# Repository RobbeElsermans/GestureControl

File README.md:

# Gesture Controlling 

Gesture controlling with X-NUCLEO-53L3A2 DevKit.

Developed by Robbe Elsermans With ED&A.

Info over de code is te vinden [hier](https://robbeelsermans.github.io/GestureControl/#/).

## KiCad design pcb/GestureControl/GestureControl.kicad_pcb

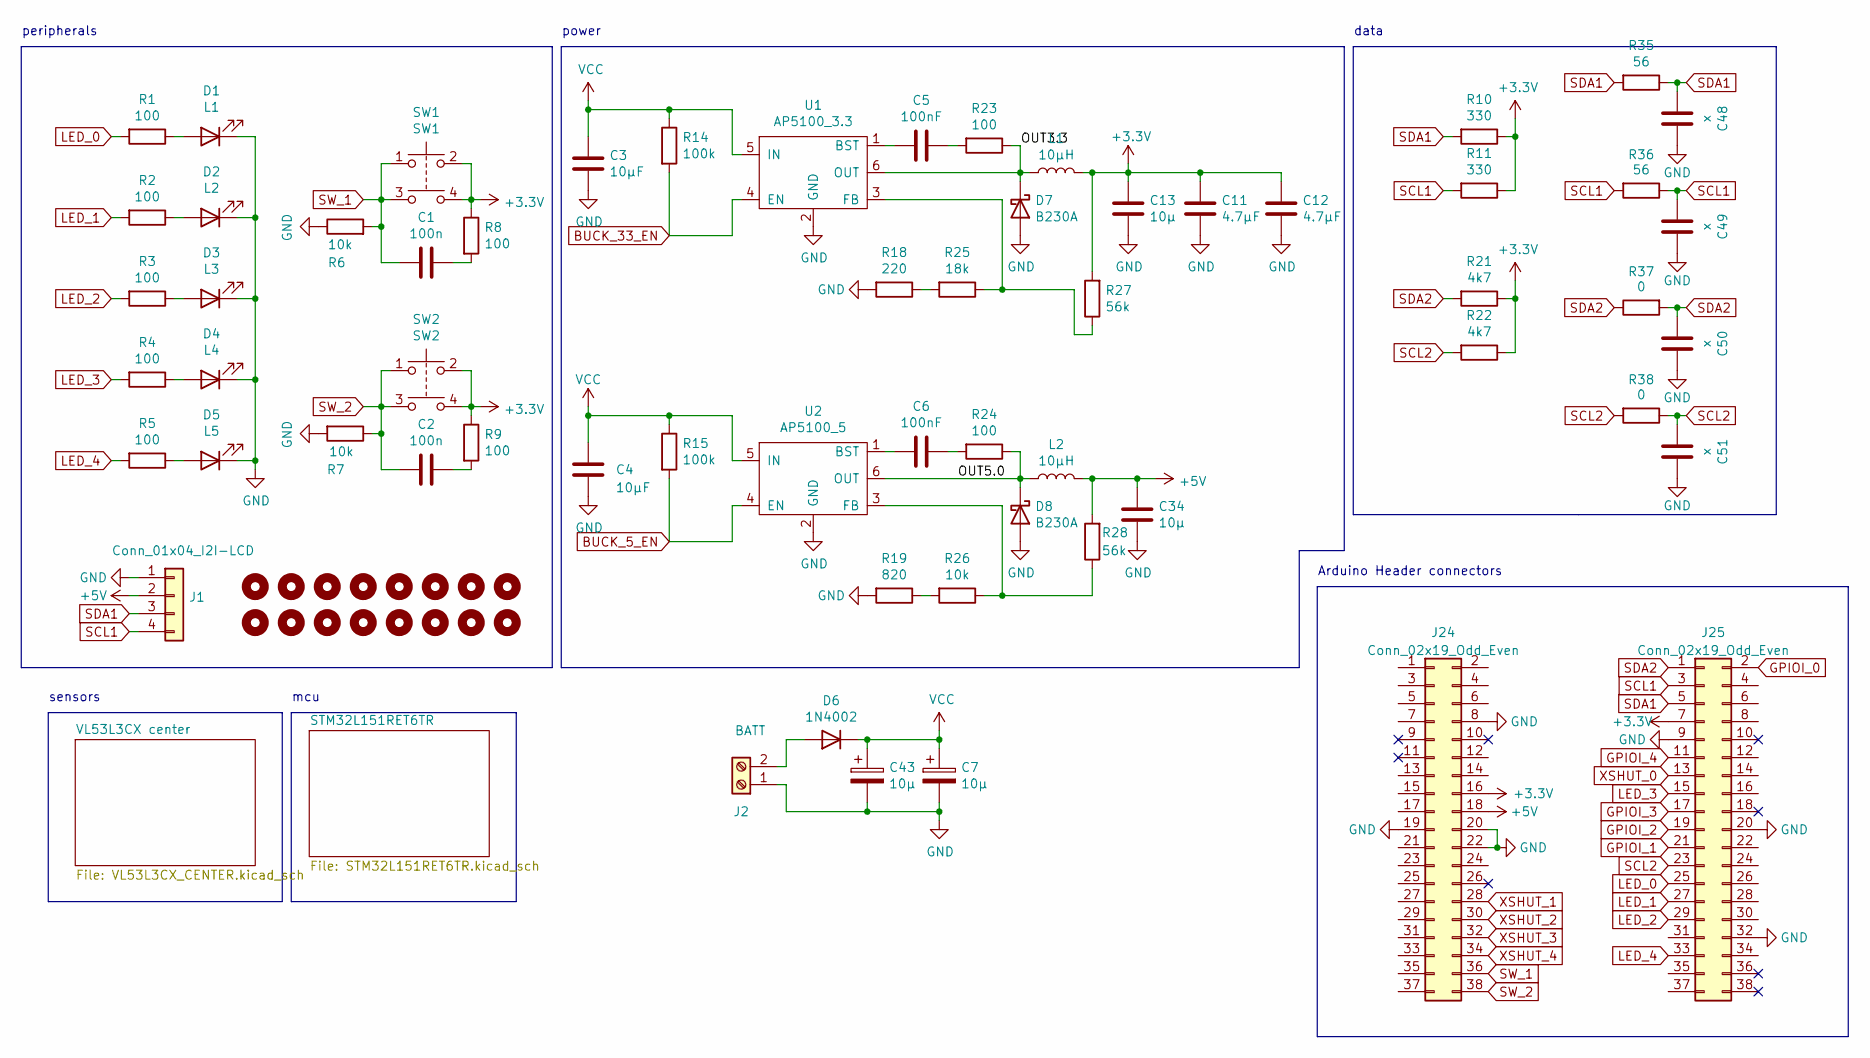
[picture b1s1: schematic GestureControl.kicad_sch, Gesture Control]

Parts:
C1, C2: 100n; C_0603_1608Metric_Pad1.08x0.95mm_HandSolder
C3, C4: 10µF; C_1206_3216Metric_Pad1.33x1.80mm_HandSolder
C5, C6: 100nF; C_0603_1608Metric_Pad1.08x0.95mm_HandSolder
C7, C43: 10µ; CP_Elec_6.3x5.4
C11, C12: 4.7µF; C_0805_2012Metric_Pad1.18x1.45mm_HandSolder
C13, C34: 10µ; C_1206_3216Metric_Pad1.33x1.80mm_HandSolder
C48, C49, C50, C51: x; C_0805_2012Metric_Pad1.18x1.45mm_HandSolder
D1: L1; LED_0805_2012Metric_Pad1.15x1.40mm_HandSolder
D2: L2; LED_0805_2012Metric_Pad1.15x1.40mm_HandSolder
D3: L3; LED_0805_2012Metric_Pad1.15x1.40mm_HandSolder
D4: L4; LED_0805_2012Metric_Pad1.15x1.40mm_HandSolder
D5: L5; LED_0805_2012Metric_Pad1.15x1.40mm_HandSolder
D6: 1N4002; D_SMA_Handsoldering
D7, D8: B230A; D_SMA_Handsoldering
H1, H2, H3, H4, H5, H6, H7, H8, H9, H10, H11, H12, H13, H14, H15, H16: MountingHole; MountingHole_3.2mm_M3
J1: Conn_01x04_I2I-LCD; PinHeader_1x04_P2.54mm_Vertical
J2: BATT; PhoenixContact_MC_1,5_2-G-3.5_1x02_P3.50mm_Horizontal
J24, J25: Conn_02x19_Odd_Even; PinSocket_2x19_P2.54mm_Vertical
L1, L2: 10µH; L_Taiyo-Yuden_NR-50xx_HandSoldering
R1, R2, R3, R4, R5, R8, R9, R23, R24: 100; R_0805_2012Metric_Pad1.20x1.40mm_HandSolder
R6, R7, R26: 10k; R_0805_2012Metric_Pad1.20x1.40mm_HandSolder
R10, R11: 330; R_0805_2012Metric_Pad1.20x1.40mm_HandSolder
R14, R15: 100k; R_0805_2012Metric_Pad1.20x1.40mm_HandSolder
R18: 220; R_0805_2012Metric_Pad1.20x1.40mm_HandSolder
R19: 820; R_0805_2012Metric_Pad1.20x1.40mm_HandSolder
R21, R22: 4k7; R_0805_2012Metric_Pad1.20x1.40mm_HandSolder
R25: 18k; R_0805_2012Metric_Pad1.20x1.40mm_HandSolder
R27, R28: 56k; R_0805_2012Metric_Pad1.20x1.40mm_HandSolder
R35, R36: 56; R_0805_2012Metric_Pad1.20x1.40mm_HandSolder
R37, R38: 0; R_0805_2012Metric_Pad1.20x1.40mm_HandSolder
SW1: SW1; SW_Push_1P1T_NO_6x6mm_H9.5mm
SW2: SW2; SW_Push_1P1T_NO_6x6mm_H9.5mm
U1: AP5100_3.3; TSOT-23-6_HandSoldering
U2: AP5100_5; TSOT-23-6_HandSoldering

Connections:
+3V3: C11.1, C12.1, C13.1, J24.16, J25.7, L1.2, R8.1, R9.1, R10.1, R11.1, R21.1, R22.1, R27.2, SW1.2, SW1.4, SW2.2, SW2.4; also elsewhere on the board
+5V: C34.1, J1.2, J24.18, L2.2, R28.2; also elsewhere on the board
/OUT3.3: D7.1 (K), L1.1, R23.1, U1.6 (OUT)
/OUT5.0: D8.1 (K), L2.1, R24.1, U2.6 (OUT)
BUCK_5_EN: R15.2, U2.4 (EN); also elsewhere on the board
BUCK_33_EN: R14.2, U1.4 (EN)
GND: C3.2, C4.2, C7.2, C11.2, C12.2, C13.2, C34.2, C43.2, C48.1, C49.1, C50.1, C51.1, D1.1 (K), D2.1 (K), D3.1 (K), D4.1 (K), D5.1 (K), D7.2 (A), D8.2 (A), J1.1, J2.1, J24.8, J24.19, J24.20, J24.22, J25.9, J25.20, J25.32, R6.1, R7.2, R18.2, R19.2, U1.2 (GND), U2.2 (GND); also elsewhere on the board
GPIOI_0: J25.2; also elsewhere on the board
GPIOI_1: J25.21; also elsewhere on the board
GPIOI_2: J25.19; also elsewhere on the board
GPIOI_3: J25.17; also elsewhere on the board
GPIOI_4: J25.11; also elsewhere on the board
LED_0: J25.25, R1.2; also elsewhere on the board
LED_1: J25.27, R2.2; also elsewhere on the board
LED_2: J25.29, R3.2; also elsewhere on the board
LED_3: J25.15, R4.2; also elsewhere on the board
LED_4: J25.33, R5.2; also elsewhere on the board
unnamed: C1.1, R8.2
unnamed: C2.1, R9.2
unnamed: C5.1, R23.2
unnamed: C5.2, U1.1 (BST)
unnamed: C6.1, R24.2
unnamed: C6.2, U2.1 (BST)
unnamed: D1.2 (A), R1.1
unnamed: D2.2 (A), R2.1
unnamed: D3.2 (A), R3.1
unnamed: D4.2 (A), R4.1
unnamed: D5.2 (A), R5.1
unnamed: D6.2 (A), J2.2
unnamed: R18.1, R25.2
unnamed: R19.1, R26.2
unnamed: R25.1, R27.1, U1.3 (FB)
unnamed: R26.1, R28.1, U2.3 (FB)
SCL1: C49.2, J1.4, J25.3, R11.2, R36.1, R36.2; also elsewhere on the board
SCL2: C51.2, J25.23, R22.2, R38.1, R38.2; also elsewhere on the board
SDA1: C48.2, J1.3, J25.5, R10.2, R35.1, R35.2; also elsewhere on the board
SDA2: C50.2, J25.1, R21.2, R37.1, R37.2; also elsewhere on the board
SW_1: C1.2, J24.36, R6.2, SW1.1, SW1.3; also elsewhere on the board
SW_2: C2.2, J24.38, R7.1, SW2.1, SW2.3; also elsewhere on the board
VCC: C3.1, C4.1, C7.1, C43.1, D6.1 (K), R14.1, R15.1, U1.5 (IN), U2.5 (IN)
XSHUT_0: J25.13; also elsewhere on the board
XSHUT_1: J24.28; also elsewhere on the board
XSHUT_2: J24.30; also elsewhere on the board
XSHUT_3: J24.32; also elsewhere on the board
XSHUT_4: J24.34; also elsewhere on the board

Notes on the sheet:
data
sensors
Arduino Header connectors
peripherals
mcu
power

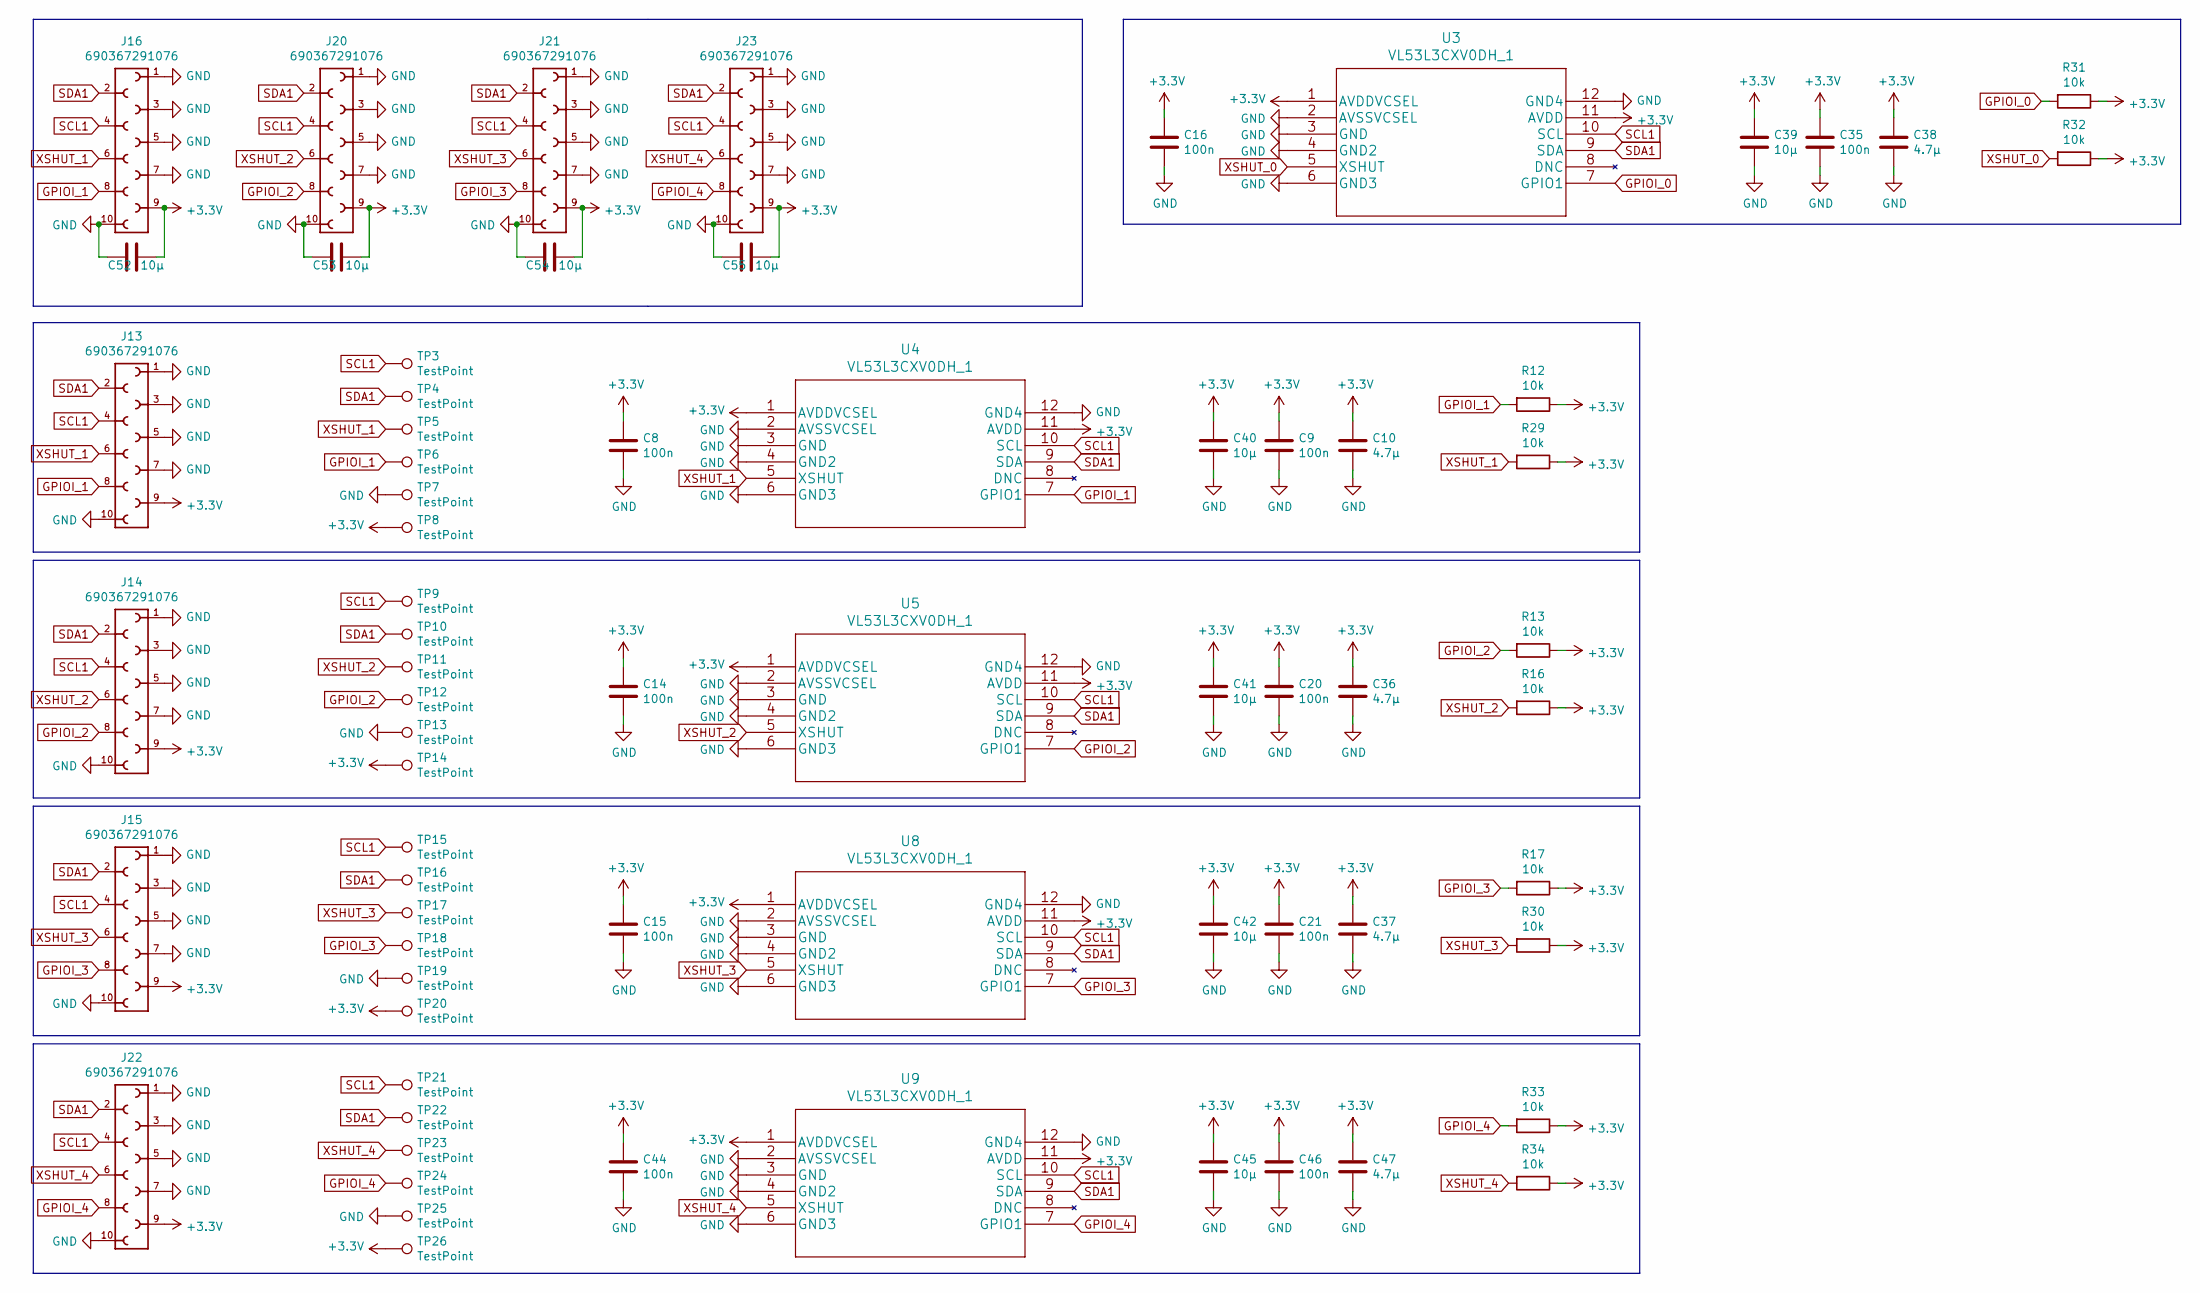
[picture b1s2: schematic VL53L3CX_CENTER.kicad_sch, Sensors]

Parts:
C8, C9, C14, C15, C16, C20, C21, C35, C44, C46: 100n; C_0603_1608Metric_Pad1.08x0.95mm_HandSolder
C10, C36, C37, C38, C47: 4.7µ; C_0805_2012Metric_Pad1.18x1.45mm_HandSolder
C39, C40, C41, C42, C45, C52, C53, C54, C55: 10µ; C_1206_3216Metric_Pad1.33x1.80mm_HandSolder
J13, J14, J15, J16, J20, J21, J22, J23: 690367291076; WR-MM_Female_SMT_Connector; PART-NUMBER 690367291076
R12, R13, R16, R17, R29, R30, R31, R32, R33, R34: 10k; R_0805_2012Metric_Pad1.20x1.40mm_HandSolder
TP3, TP4, TP5, TP6, TP7, TP8, TP9, TP10, TP11, TP12, TP13, TP14, TP15, TP16, TP17, TP18, TP19, TP20, TP21, TP22, TP23, TP24, TP25, TP26: TestPoint; TestPoint_Pad_D2.0mm
U3, U4, U5, U8, U9: VL53L3CXV0DH_1; VL53L3CXV0DH&slash_1

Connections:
+3V3: C8.1, C9.1, C10.1, C14.1, C15.1, C16.1, C20.1, C21.1, C35.1, C36.1, C37.1, C38.1, C39.1, C40.1, C41.1, C42.1, C44.1, C45.1, C46.1, C47.1, C52.1, C53.1, C54.1, C55.1, J13.9, J14.9, J15.9, J16.9, J20.9, J21.9, J22.9, J23.9, R12.1, R13.1, R16.1, R17.1, R29.1, R30.1, R31.1, R32.1, R33.1, R34.1, TP8.1, TP14.1, TP20.1, TP26.1, U3.1 (AVDDVCSEL), U3.11 (AVDD), U4.1 (AVDDVCSEL), U4.11 (AVDD), U5.1 (AVDDVCSEL), U5.11 (AVDD), U8.1 (AVDDVCSEL), U8.11 (AVDD), U9.1 (AVDDVCSEL), U9.11 (AVDD); also elsewhere on the board
GND: C8.2, C9.2, C10.2, C14.2, C15.2, C16.2, C20.2, C21.2, C35.2, C36.2, C37.2, C38.2, C39.2, C40.2, C41.2, C42.2, C44.2, C45.2, C46.2, C47.2, C52.2, C53.2, C54.2, C55.2, J13.1, J13.3, J13.5, J13.7, J13.10, J14.1, J14.3, J14.5, J14.7, J14.10, J15.1, J15.3, J15.5, J15.7, J15.10, J16.1, J16.3, J16.5, J16.7, J16.10, J20.1, J20.3, J20.5, J20.7, J20.10, J21.1, J21.3, J21.5, J21.7, J21.10, J22.1, J22.3, J22.5, J22.7, J22.10, J23.1, J23.3, J23.5, J23.7, J23.10, TP7.1, TP13.1, TP19.1, TP25.1, U3.2 (AVSSVCSEL), U3.3 (GND), U3.4 (GND2), U3.6 (GND3), U3.12 (GND4), U4.2 (AVSSVCSEL), U4.3 (GND), U4.4 (GND2), U4.6 (GND3), U4.12 (GND4), U5.2 (AVSSVCSEL), U5.3 (GND), U5.4 (GND2), U5.6 (GND3), U5.12 (GND4), U8.2 (AVSSVCSEL), U8.3 (GND), U8.4 (GND2), U8.6 (GND3), U8.12 (GND4), U9.2 (AVSSVCSEL), U9.3 (GND), U9.4 (GND2), U9.6 (GND3), U9.12 (GND4); also elsewhere on the board
GPIOI_0: R31.2, U3.7 (GPIO1); also elsewhere on the board
GPIOI_1: J13.8, J16.8, R12.2, TP6.1, U4.7 (GPIO1); also elsewhere on the board
GPIOI_2: J14.8, J20.8, R13.2, TP12.1, U5.7 (GPIO1); also elsewhere on the board
GPIOI_3: J15.8, J21.8, R17.2, TP18.1, U8.7 (GPIO1); also elsewhere on the board
GPIOI_4: J22.8, J23.8, R33.2, TP24.1, U9.7 (GPIO1); also elsewhere on the board
SCL1: J13.4, J14.4, J15.4, J16.4, J20.4, J21.4, J22.4, J23.4, TP3.1, TP9.1, TP15.1, TP21.1, U3.10 (SCL), U4.10 (SCL), U5.10 (SCL), U8.10 (SCL), U9.10 (SCL); also elsewhere on the board
SDA1: J13.2, J14.2, J15.2, J16.2, J20.2, J21.2, J22.2, J23.2, TP4.1, TP10.1, TP16.1, TP22.1, U3.9 (SDA), U4.9 (SDA), U5.9 (SDA), U8.9 (SDA), U9.9 (SDA); also elsewhere on the board
XSHUT_0: R32.2, U3.5 (XSHUT); also elsewhere on the board
XSHUT_1: J13.6, J16.6, R29.2, TP5.1, U4.5 (XSHUT); also elsewhere on the board
XSHUT_2: J14.6, J20.6, R16.2, TP11.1, U5.5 (XSHUT); also elsewhere on the board
XSHUT_3: J15.6, J21.6, R30.2, TP17.1, U8.5 (XSHUT); also elsewhere on the board
XSHUT_4: J22.6, J23.6, R34.2, TP23.1, U9.5 (XSHUT); also elsewhere on the board

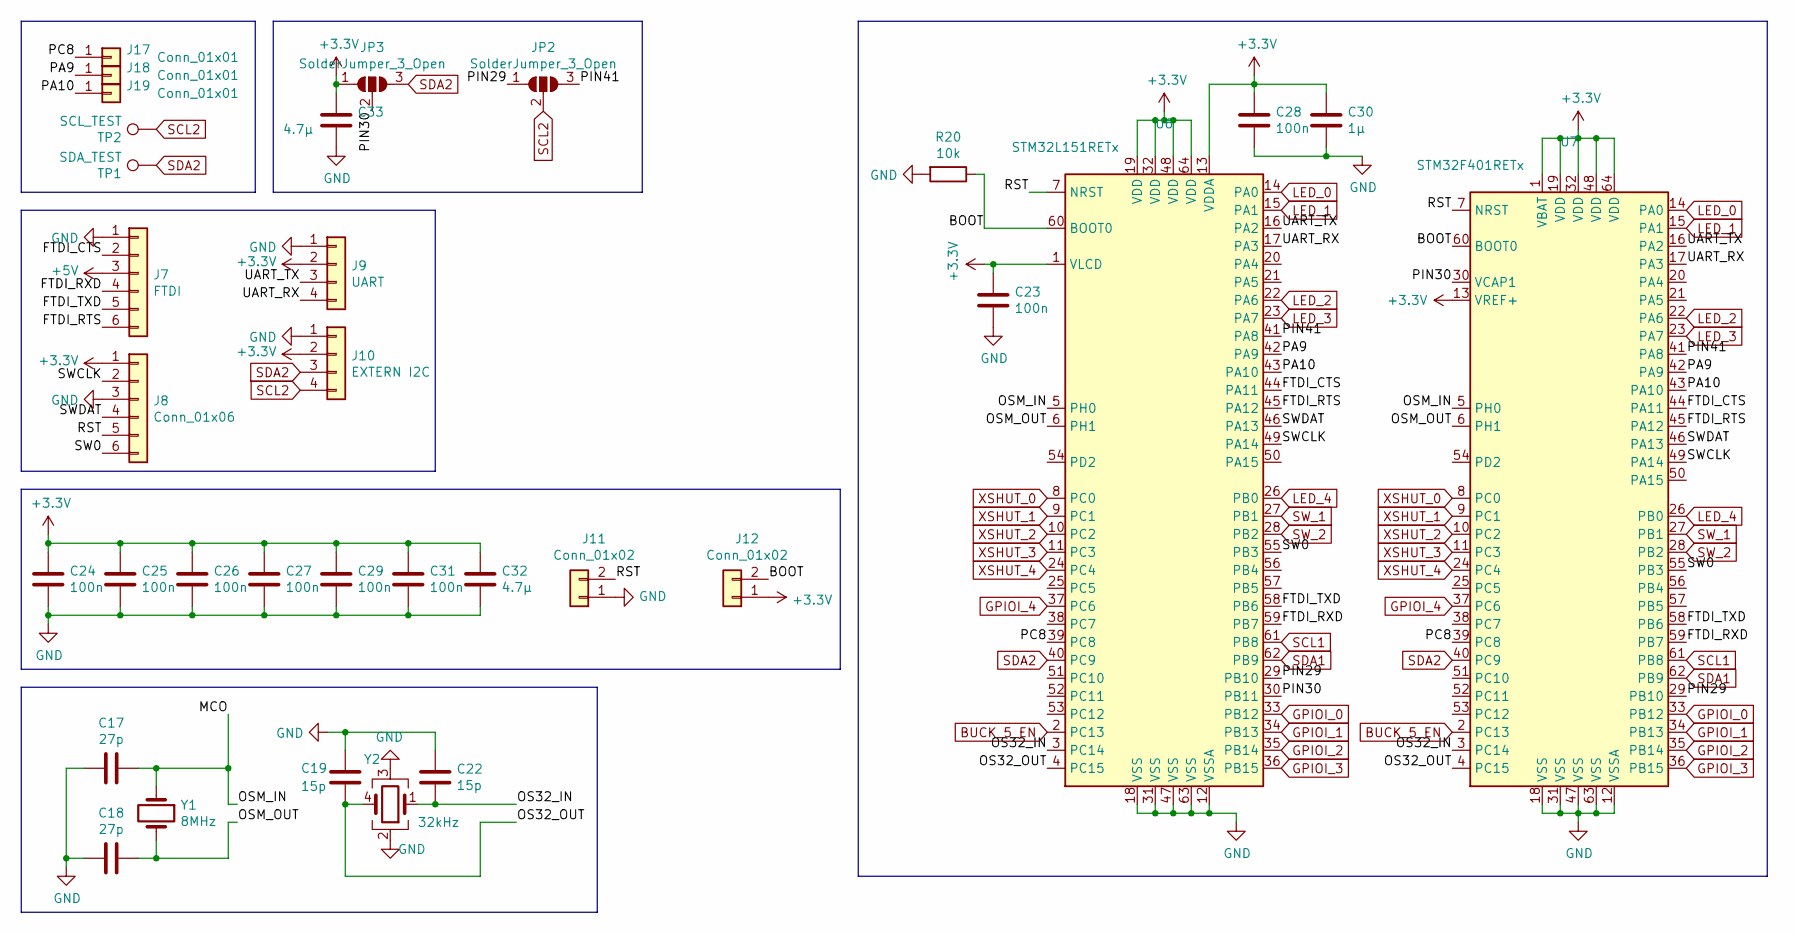
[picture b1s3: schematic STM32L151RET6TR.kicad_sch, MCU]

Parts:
C17, C18: 27p; C_0805_2012Metric_Pad1.18x1.45mm_HandSolder
C19, C22: 15p; C_0603_1608Metric_Pad1.08x0.95mm_HandSolder
C23, C24, C25, C26, C27, C28, C29, C31: 100n; C_0603_1608Metric_Pad1.08x0.95mm_HandSolder
C30: 1µ; C_0805_2012Metric_Pad1.18x1.45mm_HandSolder
C32, C33: 4.7µ; C_0805_2012Metric_Pad1.18x1.45mm_HandSolder
J7: FTDI; PinHeader_1x06_P2.54mm_Vertical
J8: Conn_01x06; PinHeader_1x06_P2.54mm_Vertical
J9: UART; PinHeader_1x04_P2.54mm_Vertical
J10: EXTERN I2C; PinHeader_1x04_P2.54mm_Vertical
J11, J12: Conn_01x02; PinHeader_1x02_P2.54mm_Vertical
J17, J18, J19: Conn_01x01; TestPoint_Pad_1.5x1.5mm
JP2, JP3: SolderJumper_3_Open; SolderJumper-3_P1.3mm_Open_RoundedPad1.0x1.5mm_NumberLabels
R20: 10k; R_0805_2012Metric_Pad1.20x1.40mm_HandSolder
TP1: SDA_TEST; TestPoint_Pad_1.0x1.0mm
TP2: SCL_TEST; TestPoint_Pad_1.0x1.0mm
U6: STM32L151RETx; LQFP-64_10x10mm_P0.5mm
U7: STM32F401RETx; LQFP-64_10x10mm_P0.5mm
Y1: 8MHz; Crystal_SMD_HC49-SD
Y2: 32kHz; Crystal_SMD_SeikoEpson_MC306-4Pin_8.0x3.2mm

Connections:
+3V3: C23.1, C24.1, C25.1, C26.1, C27.1, C28.1, C29.1, C30.1, C31.1, C32.1, C33.1, J8.1, J9.2, J10.2, J12.1, JP3.1 (A), U6.1 (VLCD), U6.13 (VDDA), U6.19 (VDD), U6.32 (VDD), U6.48 (VDD), U6.64 (VDD), U7.1 (VBAT), U7.13 (VREF+), U7.19 (VDD), U7.32 (VDD), U7.48 (VDD), U7.64 (VDD); also elsewhere on the board
+5V: J7.3; also elsewhere on the board
/STM32L151RET6TR/BOOT: J12.2, R20.1, U6.60 (BOOT0), U7.60 (BOOT0)
/STM32L151RET6TR/FTDI_CTS: J7.2, U6.44 (PA11), U7.44 (PA11)
/STM32L151RET6TR/FTDI_RTS: J7.6, U6.45 (PA12), U7.45 (PA12)
/STM32L151RET6TR/FTDI_RXD: J7.4, U6.59 (PB7), U7.59 (PB7)
/STM32L151RET6TR/FTDI_TXD: J7.5, U6.58 (PB6), U7.58 (PB6)
/STM32L151RET6TR/MCO: C17.1, U6.5 (PH0), U7.5 (PH0), Y1.1
/STM32L151RET6TR/OS32_IN: C22.2, U6.3 (PC14), U7.3 (PC14), Y2.1
/STM32L151RET6TR/OS32_OUT: C19.2, U6.4 (PC15), U7.4 (PC15), Y2.4
/STM32L151RET6TR/OSM_OUT: C18.1, U6.6 (PH1), U7.6 (PH1), Y1.2
/STM32L151RET6TR/PA9: J18.1, U6.42 (PA9), U7.42 (PA9)
/STM32L151RET6TR/PA10: J19.1, U6.43 (PA10), U7.43 (PA10)
/STM32L151RET6TR/PC8: J17.1, U6.39 (PC8), U7.39 (PC8)
/STM32L151RET6TR/PIN29: JP2.1 (A), U6.29 (PB10), U7.29 (PB10)
/STM32L151RET6TR/PIN30: JP3.2 (C), U6.30 (PB11), U7.30 (VCAP1)
/STM32L151RET6TR/PIN41: JP2.3 (B), U6.41 (PA8), U7.41 (PA8)
/STM32L151RET6TR/RST: J8.5, J11.2, U6.7 (NRST), U7.7 (NRST)
/STM32L151RET6TR/SW0: J8.6, U6.55 (PB3), U7.55 (PB3)
/STM32L151RET6TR/SWCLK: J8.2, U6.49 (PA14), U7.49 (PA14)
/STM32L151RET6TR/SWDAT: J8.4, U6.46 (PA13), U7.46 (PA13)
/STM32L151RET6TR/UART_RX: J9.4, U6.17 (PA3), U7.17 (PA3)
/STM32L151RET6TR/UART_TX: J9.3, U6.16 (PA2), U7.16 (PA2)
BUCK_5_EN: U6.2 (PC13), U7.2 (PC13); also elsewhere on the board
GND: C17.2, C18.2, C19.1, C22.1, C23.2, C24.2, C25.2, C26.2, C27.2, C28.2, C29.2, C30.2, C31.2, C32.2, C33.2, J7.1, J8.3, J9.1, J10.1, J11.1, R20.2, U6.12 (VSSA), U6.18 (VSS), U6.31 (VSS), U6.47 (VSS), U6.63 (VSS), U7.12 (VSSA), U7.18 (VSS), U7.31 (VSS), U7.47 (VSS), U7.63 (VSS), Y2.2, Y2.3; also elsewhere on the board
GPIOI_0: U6.33 (PB12), U7.33 (PB12); also elsewhere on the board
GPIOI_1: U6.34 (PB13), U7.34 (PB13); also elsewhere on the board
GPIOI_2: U6.35 (PB14), U7.35 (PB14); also elsewhere on the board
GPIOI_3: U6.36 (PB15), U7.36 (PB15); also elsewhere on the board
GPIOI_4: U6.37 (PC6), U7.37 (PC6); also elsewhere on the board
LED_0: U6.14 (PA0), U7.14 (PA0); also elsewhere on the board
LED_1: U6.15 (PA1), U7.15 (PA1); also elsewhere on the board
LED_2: U6.22 (PA6), U7.22 (PA6); also elsewhere on the board
LED_3: U6.23 (PA7), U7.23 (PA7); also elsewhere on the board
LED_4: U6.26 (PB0), U7.26 (PB0); also elsewhere on the board
SCL1: U6.61 (PB8), U7.61 (PB8); also elsewhere on the board
SCL2: J10.4, JP2.2 (C), TP2.1; also elsewhere on the board
SDA1: U6.62 (PB9), U7.62 (PB9); also elsewhere on the board
SDA2: J10.3, JP3.3 (B), TP1.1, U6.40 (PC9), U7.40 (PC9); also elsewhere on the board
SW_1: U6.27 (PB1), U7.27 (PB1); also elsewhere on the board
SW_2: U6.28 (PB2), U7.28 (PB2); also elsewhere on the board
XSHUT_0: U6.8 (PC0), U7.8 (PC0); also elsewhere on the board
XSHUT_1: U6.9 (PC1), U7.9 (PC1); also elsewhere on the board
XSHUT_2: U6.10 (PC2), U7.10 (PC2); also elsewhere on the board
XSHUT_3: U6.11 (PC3), U7.11 (PC3); also elsewhere on the board
XSHUT_4: U6.24 (PC4), U7.24 (PC4); also elsewhere on the board

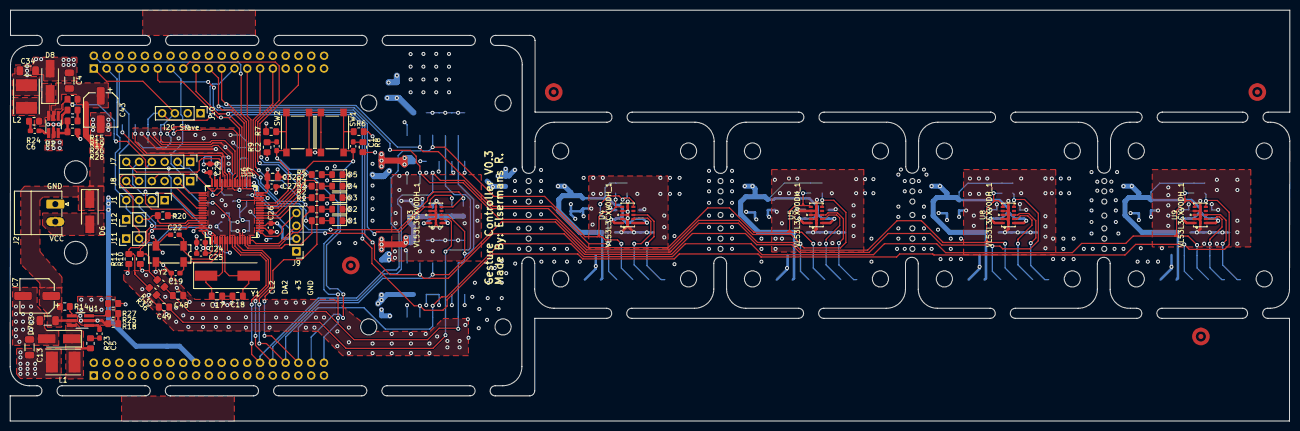
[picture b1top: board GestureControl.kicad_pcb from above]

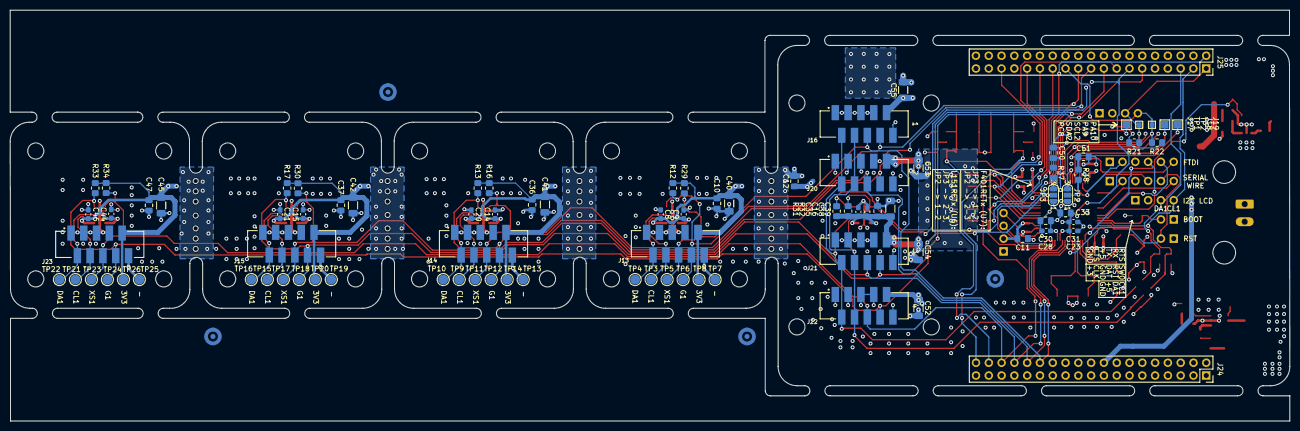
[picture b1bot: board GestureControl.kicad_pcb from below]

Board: 4 copper layers, 254.1 x 81.6 mm, 185 parts (88 on the bottom side), 66 nets.

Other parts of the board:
H13#2, H14#2, H15#2, H16#2: MountingHole; MountingHole_3.2mm_M3

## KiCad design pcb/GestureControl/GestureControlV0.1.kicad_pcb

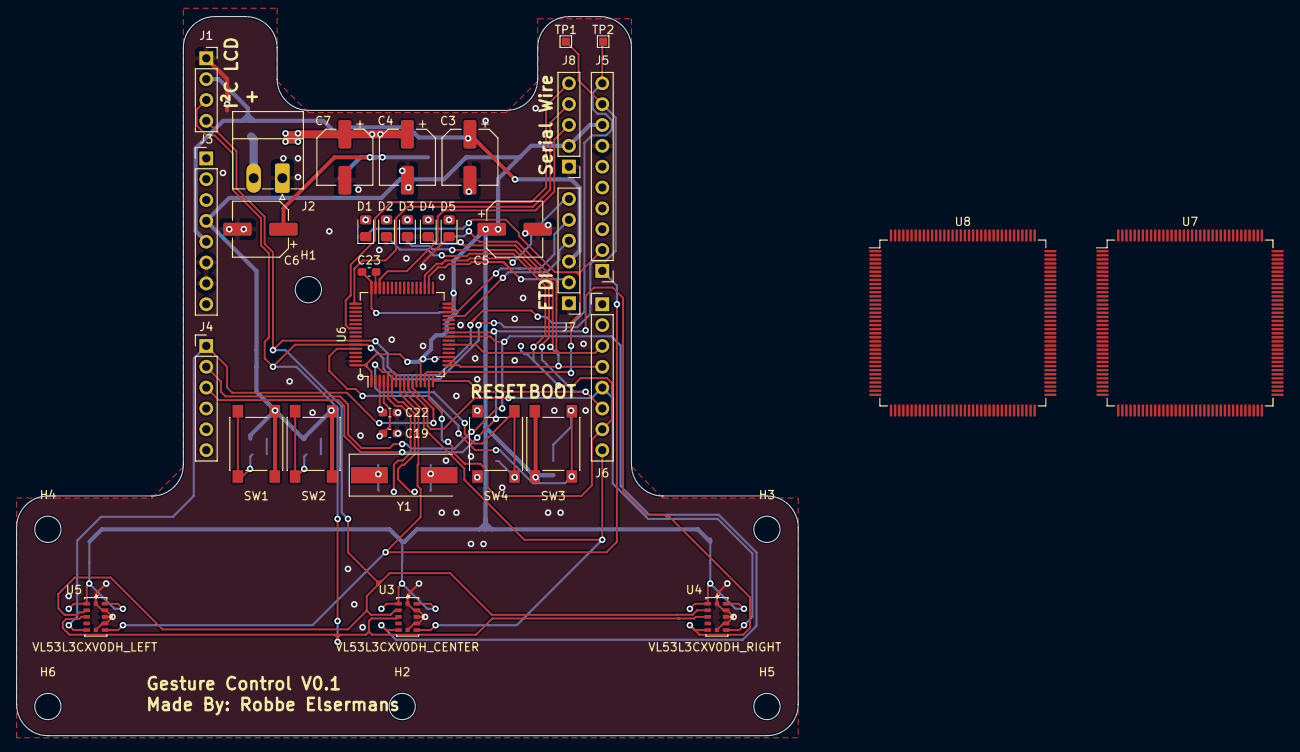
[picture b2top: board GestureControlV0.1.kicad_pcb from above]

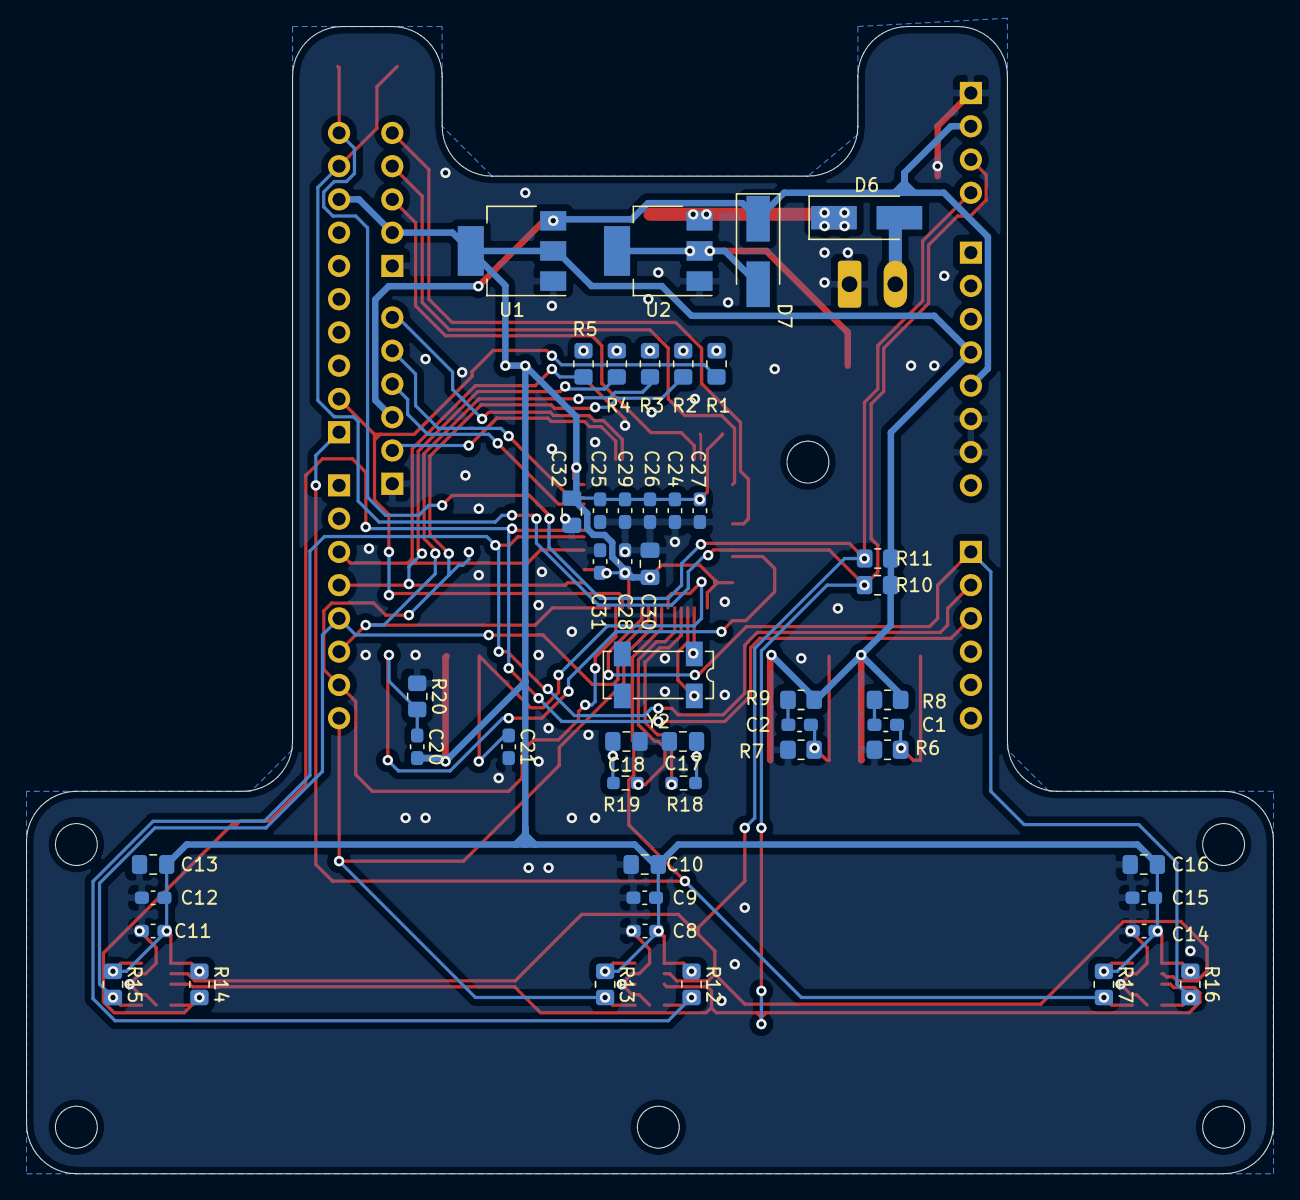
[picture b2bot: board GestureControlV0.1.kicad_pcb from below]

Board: 2 copper layers, 95.2 x 87.6 mm, 89 parts (49 on the bottom side), 43 nets.

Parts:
C1, C2, C8, C9, C11, C12, C14, C15, C20, C21, C23, C24, C25, C26, C27, C28, C29, C31: 100n; C_0603_1608Metric_Pad1.08x0.95mm_HandSolder
C3, C4, C7: 10µ; CP_Elec_6.3x5.4
C5, C6: 100µ; CP_Elec_6.3x5.4
C10, C13, C16, C32: 4.7µ; C_0805_2012Metric_Pad1.18x1.45mm_HandSolder
C17, C18: 20p; C_0805_2012Metric_Pad1.18x1.45mm_HandSolder
C19, C22: 20p; C_0603_1608Metric_Pad1.08x0.95mm_HandSolder
C30: 1µ; C_0805_2012Metric_Pad1.18x1.45mm_HandSolder
D1: L1; LED_0805_2012Metric_Pad1.15x1.40mm_HandSolder
D2: L2; LED_0805_2012Metric_Pad1.15x1.40mm_HandSolder
D3: L3; LED_0805_2012Metric_Pad1.15x1.40mm_HandSolder
D4: L4; LED_0805_2012Metric_Pad1.15x1.40mm_HandSolder
D5: L5; LED_0805_2012Metric_Pad1.15x1.40mm_HandSolder
D6, D7: 1N4002; D_SMA_Handsoldering
H1, H2, H3, H4, H5, H6: MountingHole; MountingHole_3.2mm_M3
J1: Conn_01x04_I2I-LCD; PinSocket_1x04_P2.54mm_Vertical
J2: BATT; PhoenixContact_MC_1,5_2-G-3.5_1x02_P3.50mm_Horizontal
J3, J6: Conn_01x08; PinHeader_1x08_P2.54mm_Vertical
J4: Conn_01x06; PinHeader_1x06_P2.54mm_Vertical
J5: Conn_01x10; PinHeader_1x10_P2.54mm_Vertical
J7: FTDI; PinHeader_1x06_P2.54mm_Vertical
J8: Serial Wire; PinHeader_1x05_P2.54mm_Vertical
R1, R2, R3, R4, R5, R8, R9: 100; R_0805_2012Metric_Pad1.20x1.40mm_HandSolder
R6, R7, R12, R13, R14, R15, R16, R17, R20: 10k; R_0805_2012Metric_Pad1.20x1.40mm_HandSolder
R10, R11: 4k7; R_0805_2012Metric_Pad1.20x1.40mm_HandSolder
R18, R19: N/A; R_0603_1608Metric_Pad0.98x0.95mm_HandSolder
SW1: SW1; SW_Push_1P1T_NO_6x6mm_H9.5mm
SW2: SW2; SW_Push_1P1T_NO_6x6mm_H9.5mm
SW3: BOOT; SW_Push_1P1T_NO_6x6mm_H9.5mm
SW4: RST; SW_Push_1P1T_NO_6x6mm_H9.5mm
TP1: SDA_TEST; TestPoint_Pad_1.0x1.0mm
TP2: SCL_TEST; TestPoint_Pad_1.0x1.0mm
U1: LD1117-3.3; SOT-223-3_TabPin2
U2: LD1117-5.0; SOT-223-3_TabPin2
U3: VL53L3CXV0DH_CENTER; VL53L3CXV0DH&slash_1
U4: VL53L3CXV0DH_RIGHT; VL53L3CXV0DH&slash_1
U5: VL53L3CXV0DH_LEFT; VL53L3CXV0DH&slash_1
U6: STM32L151RETx; LQFP-64_10x10mm_P0.5mm
U7: STM32L151ZCTx; LQFP-144_20x20mm_P0.5mm
U8: STM32F723ZETx; LQFP-144_20x20mm_P0.5mm
Y1: 8MHz; Crystal_SMD_HC49-SD
Y2: 32kHz; Crystal_SMD_SeikoEpson_MC306-4Pin_8.0x3.2mm

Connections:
+3V3: C5.1, C8.1, C9.1, C10.1, C11.1, C12.1, C13.1, C14.1, C15.1, C16.1, C20.2, C23.1, C24.1, C25.1, C26.1, C27.1, C28.1, C29.1, C30.1, C31.1, C32.1, J3.4, J5.8, J8.2, R8.1, R9.1, R10.1, R11.1, R12.1, R13.1, R14.1, R15.1, R16.1, R17.1, SW1.2, SW2.2, SW3.1, U1.2, U3.1, U3.11, U4.1, U4.11, U5.1, U5.11, U6.1, U6.13, U6.19, U6.32, U6.48, U6.64
+5V: C3.1, D7.1, J1.2, J3.5, J7.3, U1.3
/MCU/BOOT: C20.1, R20.1, SW3.2, U6.60
/MCU/FTDI_CTS: J7.2, U6.34
/MCU/FTDI_RTS: J7.6, U6.35
/MCU/FTDI_RXD: J7.5, U6.30
/MCU/FTDI_TXD: J7.4, U6.29
/MCU/MCO: R18.1, U6.5
/MCU/OS32_IN: C22.2, U6.3, Y2.1
/MCU/OS32_OUT: C19.2, U6.4, Y2.4
/MCU/OSM_OUT: R19.1, U6.6
/MCU/RST: C21.1, SW4.2, U6.7
/MCU/SW0: J8.5, U6.55
/MCU/SWCLK: J8.4, U6.49
/MCU/SWDAT: J8.3, U6.46
GND: C3.2, C4.2, C5.2, C6.2, C7.2, C8.2, C9.2, C10.2, C11.2, C12.2, C13.2, C14.2, C15.2, C16.2, C17.2, C18.2, C19.1, C21.2, C22.1, C23.2, C24.2, C25.2, C26.2, C27.2, C28.2, C29.2, C30.2, C31.2, C32.2, D1.1, D2.1, D3.1, D4.1, D5.1, J1.1, J2.1, J3.6, J3.7, J5.7, J7.1, J8.1, R6.1, R7.2, R20.2, SW4.1, U1.1, U2.1, U3.2, U3.3, U3.4, U3.6, U3.12, U4.2, U4.3, U4.4, U4.6, U4.12, U5.2, U5.3, U5.4, U5.6, U5.12, U6.12, U6.18, U6.31, U6.47, U6.63
GPIOI_0: J4.1, R16.2, U5.7, U6.11
GPIOI_1: J4.2, R12.2, U3.7, U6.24
GPIOI_2: J4.3, R14.2, U4.7, U6.25
LED_1: J5.2, R1.2, U6.14
LED_2: J6.7, R2.2, U6.15
LED_3: J6.6, R3.2, U6.16
LED_4: J6.4, R4.2, U6.17
LED_5: J6.3, R5.2, U6.22
unnamed: C1.1, R8.2
unnamed: C2.1, R9.2
unnamed: C6.1, D7.2, U2.2
unnamed: C17.1, R18.2, Y1.1
unnamed: C18.1, R19.2, Y1.2
unnamed: D1.2, R1.1
unnamed: D2.2, R2.1
unnamed: D3.2, R3.1
unnamed: D4.2, R4.1
unnamed: D5.2, R5.1
unnamed: D6.2, J2.2
SCL: J1.4, J5.10, R11.2, TP2.1, U3.10, U4.10, U5.10, U6.58
SDA: J1.3, J5.9, R10.2, TP1.1, U3.9, U4.9, U5.9, U6.59
SW_1: C1.2, R6.2, SW1.1
SW_2: C2.2, R7.1, SW2.1
VCC: C4.1, C7.1, D6.1, U2.3
XSHUT_0: J5.1, R17.2, U5.5, U6.8
XSHUT_1: J6.8, R13.2, U3.5, U6.9
XSHUT_2: J6.5, R15.2, U4.5, U6.10

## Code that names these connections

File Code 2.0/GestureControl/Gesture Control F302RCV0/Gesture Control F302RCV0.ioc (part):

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Mcu.Name=STM32F302R(B-C)Tx
Mcu.Package=LQFP64
Mcu.UserName=STM32F302RCTx
PA0.GPIOParameters=GPIO_Label
PA0.GPIO_Label=LED_0
PA0.Signal=GPIO_Input
PA1.GPIOParameters=GPIO_Label
PA1.GPIO_Label=LED_1
PA1.Signal=GPIO_Output
PA10.Mode=I2C
PA10.Signal=I2C2_SDA
PA11.Mode=CTS_RTS
PA11.Signal=USART1_CTS
PA12.Mode=CTS_RTS
PA12.Signal=USART1_RTS
PA13.Mode=Trace_Asynchronous_SW
PA13.Signal=SYS_JTMS-SWDIO
PA14.Mode=Trace_Asynchronous_SW
PA14.Signal=SYS_JTCK-SWCLK
PA2.Mode=Asynchronous
PA2.Signal=USART2_TX
PA3.Mode=Asynchronous
PA3.Signal=USART2_RX
PA6.GPIOParameters=GPIO_Label
PA6.GPIO_Label=LED_2
PA6.Signal=GPIO_Output
PA7.GPIOParameters=GPIO_Label
PA7.GPIO_Label=LED_3
PA7.Signal=GPIO_Output
PA9.Mode=I2C
PA9.Signal=I2C2_SCL
PB0.GPIOParameters=GPIO_Label
PB0.GPIO_Label=LED_4
PB0.Signal=GPIO_Output
PB1.GPIOParameters=GPIO_Label
PB1.GPIO_Label=SW_1
PB1.Signal=GPIO_Input
PB12.GPIOParameters=GPIO_Label
PB12.GPIO_Label=GPIOI_0
PB12.Signal=GPXTI12
PB13.GPIOParameters=GPIO_Label
PB13.GPIO_Label=GPIOI_1
PB13.Signal=GPXTI13
PB14.GPIOParameters=GPIO_Label
PB14.GPIO_Label=GPIOI_2
PB14.Signal=GPXTI14
PB15.GPIOParameters=GPIO_Label
PB15.GPIO_Label=GPIOI_3
PB15.Signal=GPXTI15
PB2.GPIOParameters=GPIO_Label
PB2.GPIO_Label=SW_2
PB2.Signal=GPIO_Input
PB3.Mode=Trace_Asynchronous_SW
PB3.Signal=SYS_JTDO-TRACESWO
PB6.Mode=Asynchronous
PB6.Signal=USART1_TX
PB7.Mode=Asynchronous
PB7.Signal=USART1_RX
PB8.Mode=I2C
PB8.Signal=I2C1_SCL
PB9.Mode=I2C
PB9.Signal=I2C1_SDA
PC0.GPIOParameters=GPIO_Label
PC0.GPIO_Label=XSHUT_0
PC0.Signal=GPIO_Output
PC1.GPIOParameters=GPIO_Label
PC1.GPIO_Label=XSHUT_1
PC1.Signal=GPIO_Output
PC14-OSC32_IN.Mode=LSE-External-Oscillator
PC14-OSC32_IN.Signal=RCC_OSC32_IN
PC15-OSC32_OUT.Mode=LSE-External-Oscillator
PC15-OSC32_OUT.Signal=RCC_OSC32_OUT
PC2.GPIOParameters=GPIO_Label
PC2.GPIO_Label=XSHUT_2
PC2.Signal=GPIO_Output
PC3.GPIOParameters=GPIO_Label
PC3.GPIO_Label=XSHUT_3
PC3.Signal=GPIO_Output
PC4.GPIOParameters=GPIO_Label
PC4.GPIO_Label=XSHUT_4
PC4.Signal=GPIO_Output
PC6.GPIOParameters=GPIO_Label
PC6.GPIO_Label=GPIOI_4
PC6.Signal=GPXTI6
PF0-OSC_IN.Mode=HSE-External-Oscillator
PF0-OSC_IN.Signal=RCC_OSC_IN
PF1-OSC_OUT.Mode=HSE-External-Oscillator
PF1-OSC_OUT.Signal=RCC_OSC_OUT
RCC.HSEPLLFreq_Value=8000000
RCC.HSE_VALUE=8000000
RCC.SYSCLKFreq_VALUE=8000000
board=custom

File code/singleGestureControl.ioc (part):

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Mcu.Name=STM32F401R(D-E)Tx
Mcu.Package=LQFP64
Mcu.UserName=STM32F401RETx
PA13.GPIOParameters=GPIO_Label
PA13.GPIO_Label=TMS
PA13.Mode=Serial_Wire
PA13.Signal=SYS_JTMS-SWDIO
PA14.GPIOParameters=GPIO_Label
PA14.GPIO_Label=TCK
PA14.Mode=Serial_Wire
PA14.Signal=SYS_JTCK-SWCLK
PA2.GPIOParameters=GPIO_Speed,GPIO_PuPd,GPIO_Label,GPIO_Mode
PA2.GPIO_Label=USART_TX
PA2.GPIO_Mode=GPIO_MODE_AF_PP
PA2.GPIO_PuPd=GPIO_NOPULL
PA2.GPIO_Speed=GPIO_SPEED_FREQ_LOW
PA2.Mode=Multiprocessor_communication
PA2.Signal=USART2_TX
PA3.GPIOParameters=GPIO_Speed,GPIO_PuPd,GPIO_Label,GPIO_Mode
PA3.GPIO_Label=USART_RX
PA3.GPIO_Mode=GPIO_MODE_AF_PP
PA3.GPIO_PuPd=GPIO_NOPULL
PA3.GPIO_Speed=GPIO_SPEED_FREQ_LOW
PA3.Mode=Multiprocessor_communication
PA3.Signal=USART2_RX
PA5.GPIOParameters=GPIO_Speed,GPIO_PuPd,GPIO_Label,GPIO_Mode
PA5.GPIO_Label=LD2 [Green Led]
PA5.GPIO_Mode=GPIO_MODE_OUTPUT_PP
PA5.GPIO_PuPd=GPIO_NOPULL
PA5.GPIO_Speed=GPIO_SPEED_FREQ_LOW
PA5.Signal=GPIO_Output
PA7.GPIOParameters=GPIO_Label
PA7.GPIO_Label=L_Y
PA7.Signal=GPIO_Input
PA8.Mode=I2C
PA8.Signal=I2C3_SCL
PB3.GPIOParameters=GPIO_Label
PB3.GPIO_Label=SWO
PB3.Signal=SYS_JTDO-SWO
PB8.Mode=I2C
PB8.Signal=I2C1_SCL
PB9.Mode=I2C
PB9.Signal=I2C1_SDA
PC13-ANTI_TAMP.GPIOParameters=GPIO_PuPd,GPIO_Label,GPIO_ModeDefaultEXTI
PC13-ANTI_TAMP.GPIO_Label=B1 [Blue PushButton]
PC13-ANTI_TAMP.GPIO_ModeDefaultEXTI=GPIO_MODE_IT_FALLING
PC13-ANTI_TAMP.GPIO_PuPd=GPIO_NOPULL
PC13-ANTI_TAMP.Signal=GPXTI13
PC14-OSC32_IN.Mode=LSE-External-Oscillator
PC14-OSC32_IN.Signal=RCC_OSC32_IN
PC15-OSC32_OUT.Mode=LSE-External-Oscillator
PC15-OSC32_OUT.Signal=RCC_OSC32_OUT
PC7.Signal=S_TIM3_CH2
PC9.Mode=I2C
PC9.Signal=I2C3_SDA
PH0\ -\ OSC_IN.Mode=HSE-External-Clock-Source
PH0\ -\ OSC_IN.Signal=RCC_OSC_IN
PH1\ -\ OSC_OUT.Mode=HSE-External-Clock-Source
PH1\ -\ OSC_OUT.Signal=RCC_OSC_OUT
RCC.HSE_VALUE=8000000
RCC.SYSCLKFreq_VALUE=84000000
RCC.SYSCLKSource=RCC_SYSCLKSOURCE_PLLCLK
board=NUCLEO-F401RE
boardIOC=true

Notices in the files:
parts and their libraries:
Copyright 2021 Accelerated Designs. All rights reserved.
